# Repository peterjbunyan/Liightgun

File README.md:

# Liightgun
Lightgun upgrade kit to utilize a wiimote camera and 4 IR points for screentracking.

Forked under original CC Attribution-ShareAlike 4.0 from [Mysli0210/Liightgun](https://github.com/Mysli0210/Liightgun)

Updated to use SMD components

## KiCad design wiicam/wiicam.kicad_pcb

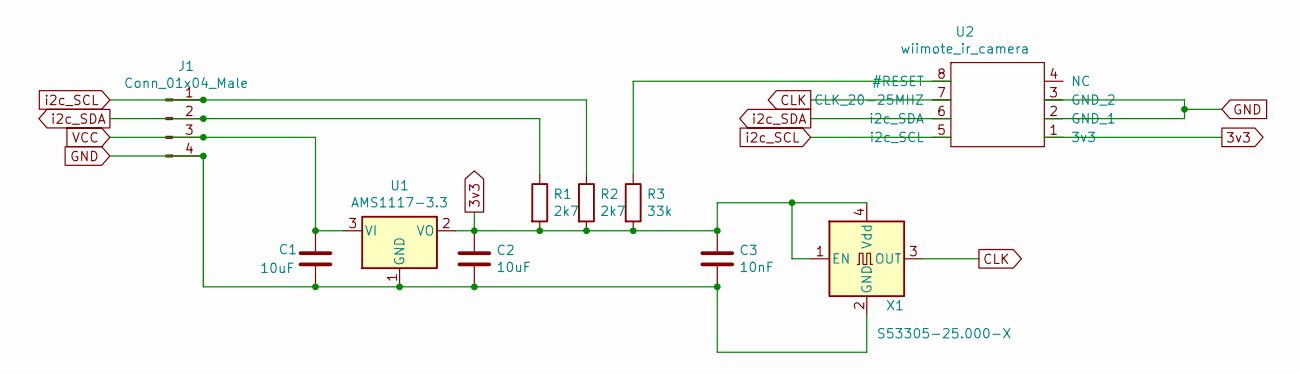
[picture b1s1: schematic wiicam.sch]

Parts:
C1, C2: 10uF; C_0805_2012Metric_Pad1.18x1.45mm_HandSolder
C3: 10nF; C_0805_2012Metric_Pad1.18x1.45mm_HandSolder
J1: Conn_01x04_Male; PinHeader_1x04_P2.54mm_Horizontal
R1, R2: 2k7; R_0805_2012Metric_Pad1.20x1.40mm_HandSolder
R3: 33k; R_0805_2012Metric_Pad1.20x1.40mm_HandSolder
U1: AMS1117-3.3; SOT-223-3_TabPin2
U2: wiimote_ir_camera; wii_ir_cam
X1: S53305-25.000-X; Oscillator_SMD_TXC_7C-4Pin_5.0x3.2mm_HandSoldering

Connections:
3v3: C2.1, C3.1, R1.2, R2.2, R3.2, U1.2 (VO), U2.1 (3v3), X1.1 (EN), X1.4 (Vdd)
CLK: U2.7 (CLK_20-25MHZ), X1.3 (OUT)
GND: C1.2, C2.2, C3.2, J1.4, U1.1 (GND), U2.2 (GND_1), U2.3 (GND_2), X1.2 (GND)
unnamed: R3.1, U2.8 (#RESET)
VCC: C1.1, J1.3, U1.3 (VI)
i2c_SCL: J1.1, R2.1, U2.5 (i2c_SCL)
i2c_SDA: J1.2, R1.1, U2.6 (i2c_SDA)

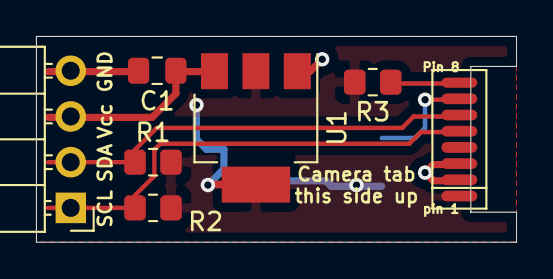
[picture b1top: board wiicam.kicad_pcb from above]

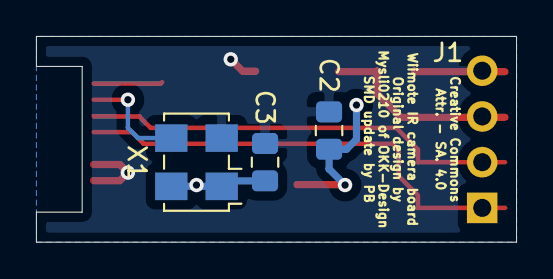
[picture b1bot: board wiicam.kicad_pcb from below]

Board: 2 copper layers, 26.7 x 11.4 mm, 10 parts (3 on the bottom side), 7 nets.

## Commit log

2022-04-29 Update with available SMD components
    Change to SMD components and change the regulator to what I have on hand
2022-04-29 Add attribution and license file
2022-04-30 Update footprint with measured pad dimensions
2022-04-30 Update PCB to SMD components and new footprint
2022-04-30 Add generated gerbers
2022-05-16 Remove OSC output capacitor Output capacitor value is too high - S53305-25.000-X is rated at max 15pF output load
2022-05-16 Added jig to help solder wiicam board to camera
2022-08-13 Add Wiicam mounting STLs

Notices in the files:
wiicam/wiicam.kicad_pcb:
Creative Commons
Attr. - SA. 4.0
